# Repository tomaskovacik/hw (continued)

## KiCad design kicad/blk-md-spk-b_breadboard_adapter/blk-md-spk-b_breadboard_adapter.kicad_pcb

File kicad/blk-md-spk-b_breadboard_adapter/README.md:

Breadboard adapter for BLK-MD-SPK-B
-----------------------------------

Breadboard adapter for the BLK-MD-SPK-B bluetooth audio module from ebay (search for BLK-MD-SPK-B) based on OVC3860 chip (not CSR!!!).

#### Adapter features

- 6 buttons(reset, play/pause, volume up/down, song previous/next)
- 3.5mm jack for headphones with direct connection, no caps
- 3.5mm jack for microphone with supporting circut
- indication leds

#### Schematics

#### Photos

bottom view, assembled unit, with BT module soldered (silk screen marking of C3/R4 was swapped, fix it with perm. marker)

#### Assembly plan

#### Arduino support 

Arduino library on github is [here](https://github.com/tomaskovacik/OVC3860/), currently in something like Beta stage, commit/suggestions are welcome

#### Additional files used in this project

Github repository with [KiCad library part](https://github.com/tomaskovacik/kicad-library/tree/master/library), [KiCad footprint](https://github.com/tomaskovacik/kicad-library/tree/master/bluetooth.pretty).

Github repository with [datasheet](https://github.com/tomaskovacik/kicad-library/tree/master/library/datasheet/).

#### Buy one

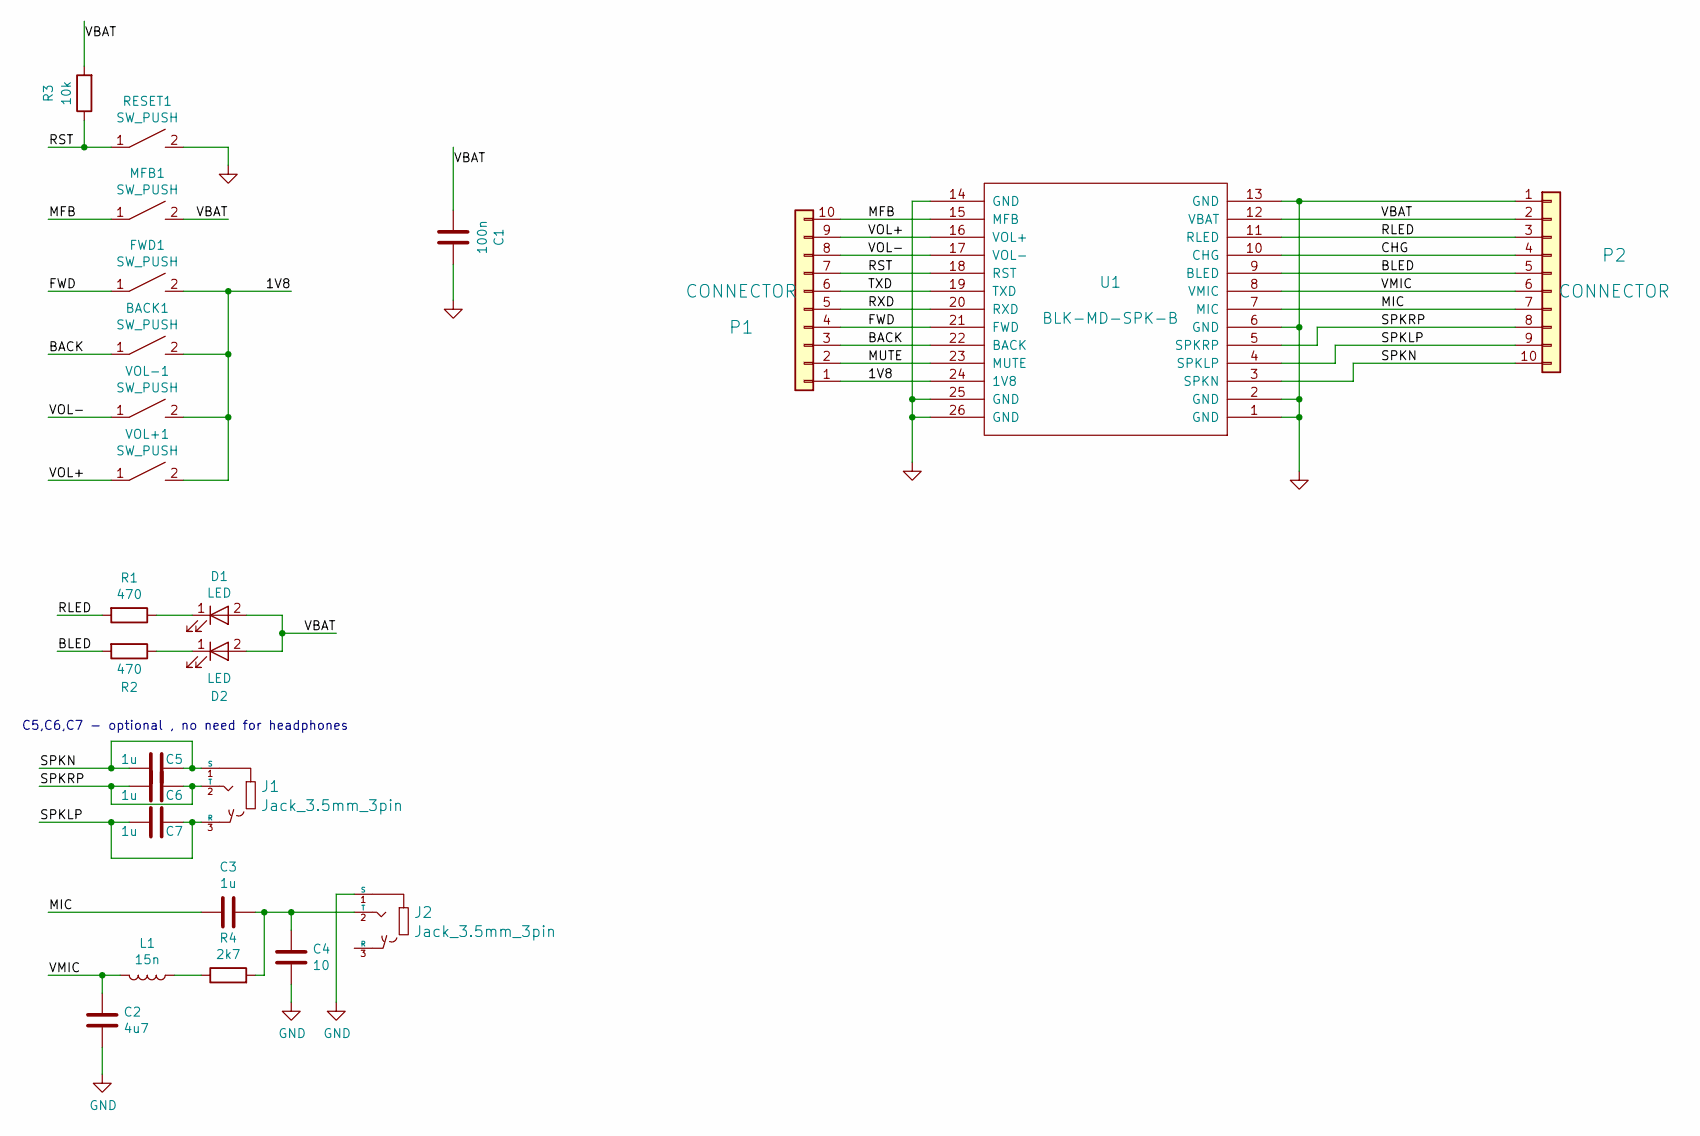
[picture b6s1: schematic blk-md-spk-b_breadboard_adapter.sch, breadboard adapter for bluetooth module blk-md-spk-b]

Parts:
BACK1: SW_PUSH; SW_SPST_FSMSM
C1: 100n; C_0805_HandSoldering
C2: 4u7; C_1206_HandSoldering
C3, C5, C6, C7: 1u; C_1206_HandSoldering
C4: 10; C_0805_HandSoldering
D1, D2: LED; LED-1206
FWD1: SW_PUSH; SW_SPST_FSMSM
J1, J2: Jack_3.5mm_3pin; 3.5mm_stereo_jack_PJ320B
L1: 15n; Choke_SMD_1206_Handsoldering
MFB1: SW_PUSH; SW_SPST_FSMSM
P1, P2: CONNECTOR; Pin_Header_Straight_1x10
R1, R2: 470; R_0805_HandSoldering
R3: 10k; R_0805_HandSoldering
R4: 2k7; R_0805_HandSoldering
RESET1: SW_PUSH; SW_SPST_FSMSM
U1: BLK-MD-SPK-B; BLK-MD-SPK-B_no_up_silk
VOL+1: SW_PUSH; SW_SPST_FSMSM
VOL-1: SW_PUSH; SW_SPST_FSMSM

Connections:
/1V8: BACK1.2, FWD1.2, P1.1, U1.24 (1V8), VOL+1.2, VOL-1.2
/BACK: BACK1.1, P1.3, U1.22 (BACK)
/BLED: P2.5, R2.2, U1.9 (BLED)
/CHG: P2.4, U1.10 (CHG)
/FWD: FWD1.1, P1.4, U1.21 (FWD)
/MFB: MFB1.1, P1.10, U1.15 (MFB)
/MIC: C3.2, P2.7, U1.7 (MIC)
/MUTE: P1.2, U1.23 (MUTE)
/RLED: P2.3, R1.2, U1.11 (RLED)
/RST: P1.7, R3.1, RESET1.1, U1.18 (RST)
/RXD: P1.5, U1.20 (RXD)
/SPKLP: C7.1, C7.2, J1.3 (R), P2.9, U1.4 (SPKLP)
/SPKN: C5.1, C5.2, J1.1 (S), P2.10, U1.3 (SPKN)
/SPKRP: C6.1, C6.2, J1.2 (T), P2.8, U1.5 (SPKRP)
/TXD: P1.6, U1.19 (TXD)
/VBAT: C1.2, D1.2 (A), D2.2 (A), MFB1.2, P2.2, R3.2, U1.12 (VBAT)
/VMIC: C2.1, L1.2, P2.6, U1.8 (VMIC)
/VOL+: P1.9, U1.16 (VOL+), VOL+1.1
/VOL-: P1.8, U1.17 (VOL-), VOL-1.1
GND: C1.1, C2.2, C4.2, J2.1 (S), P2.1, RESET1.2, U1.1 (GND), U1.2 (GND), U1.6 (GND), U1.13 (GND), U1.14 (GND), U1.25 (GND), U1.26 (GND)
unnamed: C3.1, C4.1, J2.2 (T), R4.2
unnamed: D1.1 (K), R1.1
unnamed: D2.1 (K), R2.1
unnamed: L1.1, R4.1

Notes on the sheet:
C5,C6,C7 - optional , no need for headphones

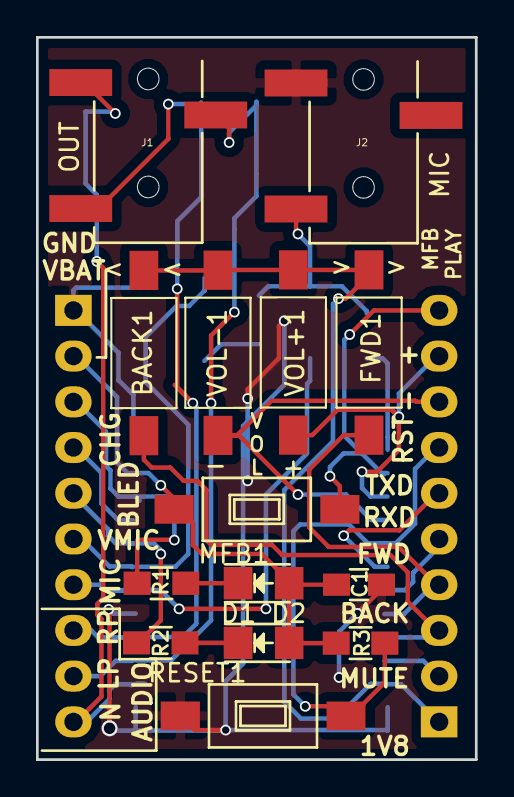
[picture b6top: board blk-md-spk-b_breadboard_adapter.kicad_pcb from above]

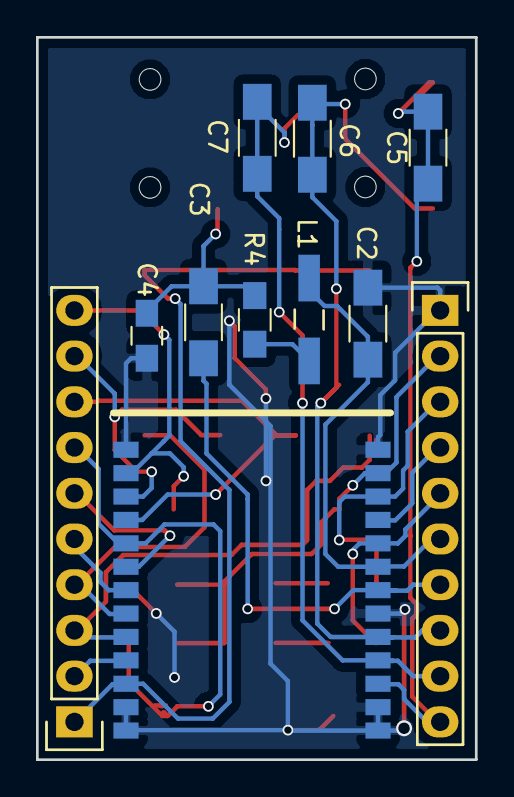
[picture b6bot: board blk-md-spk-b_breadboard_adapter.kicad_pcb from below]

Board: 2 copper layers, 24.4 x 40.1 mm, 25 parts (11 on the bottom side), 24 nets.

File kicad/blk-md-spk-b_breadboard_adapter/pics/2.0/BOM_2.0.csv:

"Id";"Designator";"Package";"Quantity";"Designation";"Supplier and ref";
1;"RESET,MFB/PLAY,BACK,FWD,VOL+,VOL-";"SW_SPST_FSMSM";6;"SW_PUSH";;;
2;"J1,J2";"3.5mm_stereo_jack_PJ320B";2;"Jack_3.5mm_3pin";;;
3;"P2,P1";"Pin_Header_Straight_1x10";2;"CONNECTOR";;;
4;"U1";"BLK-MD-SPK-B_no_up_silk";1;"BLK-MD-SPK-B";;;
5;"R2,R1";"R_0805_HandSoldering";2;"470";;;
6;"D2,D1";"LED-1206";2;"LED";;;
7;"C1";"C_0805_HandSoldering";1;"100n";;;
8;"R3";"R_0805_HandSoldering";1;"10k";;;
9;"C2";"C_1206_HandSoldering";1;"4u7";;;
10;"C3";"C_1206_HandSoldering";1;"1u";;;
11;"C4";"C_0805_HandSoldering";1;"10";;;
12;"L1";"Choke_SMD_1206_Handsoldering";1;"15n";;;
13;"R4";"R_0805_HandSoldering";1;"2k7";;;
